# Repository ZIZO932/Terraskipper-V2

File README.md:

# Terraskipper V2 

> A mudskipper-inspired soft robot built to help farmers monitor and understand their soil

---

## What is this?

Terraskipper is a robot that moves like a mudskipper fish. It crawls on mud and uneven ground using fins powered by DC motors and servos. While it moves around it collects soil data like pH levels, moisture, salinity and other environmental readings.

The whole idea came from a real problem. The Nile Delta in Egypt is facing serious soil degradation. Salt levels are rising and pH is shifting in ways that hurt farming. Most monitoring tools cant really reach difficult terrain or muddy areas. Terraskipper can.

The robot is designed to go where normal sensors cant and give farmers useful data about their land without them having to do much.

---

## Why I made it

I wanted to build something that actually solves a problem in the real world not just a cool robot for the sake of it. Agriculture in Egypt especially near the Nile Delta depends on soil quality and right now that soil is changing in ways that are hard to track.

A mudskipper felt like the perfect inspiration because it literally evolved to handle the transition between water and land which is exactly the kind of terrain that is hard for robots to deal with.

---

## Build Process

After the design was done I moved on to actually building it. A lot of stuff that worked on screen didnt work the same in real life.

- Rebuilt the circuit from the schematic one component at a time, testing power, then the Pico, then each sensor one by one (moisture, TDS, temperature, the 3 ultrasonics) so debugging was easier.
- Got PCB review feedback: add screw mounting, clean up and round the layout, include Gerber files, add the missing sensors to the CAD. Fixed all of it and gave the PCB its own mounting spot in the 3D model.
- Assembled the robot: joined the two printed body halves, built the sensor placement mechanism, mounted the motors and fins, then fit the PCB and wired everything inside the body.
- Tested the full system and tested power, sensors, and movement again after assembly to catch anything that shifted.
- Uploaded and ran the code function by function. Found the right DC motor wasnt moving, swapped both motors to confirm it wasnt the motor itself, traced it to the motor driver's motor B output, and fixed it.
- Did a final pass before filming: checked all connections, cleaned up the wiring, and ran through the movements a few times to make sure they'd look good on camera.

---

## The Final Build

after the first prototype i went back and reprinted the whole body smaller than before. still fits everything inside the same as before, just uses less filament and ends up alot lighter overall. checked all the parts lined up right after printing and made a couple small tweaks where they didnt.

that was really the only change from the first prototype to the final one, just the size.

---

## How it works

The robot has two main systems working together

**Movement system**
- Two JGB37-520 DC Geared Motors (12V 37RPM with encoders) power the pectoral fins for forward movement
- One servo controls the caudal fin for steering
- Two more servos handle the sensor placement mechanism so the sensors can move up and down to properly contact the soil

**Sensor system**
- 3x HC-SR04 ultrasonic sensors for obstacle detection and movement awareness (removed two in the final because one of them wasnt working for no reason)
- MPU-6050 IMU for tilt and orientation tracking using gyroscope and accelerometer
- Ublox NEO-7M GPS module for location tracking
- Capacitive soil moisture sensor V2.0 for soil water content readings
- DS18B20 waterproof temperature sensor for soil temperature

**Brain**
- Raspberry Pi Pico 2 W handles everything

---

## The 3D Model

For the body i made sure that all edges have fillets and chamfers so the robot doesnt damage the soil while crawling.

The sensor placement mechanism uses a mini linear slider with a servo motor so the sensors can move vertically and make proper contact with different soil surfaces. The mechanism is also detachable so it can be removed for repairs without taking apart the whole robot.

---

## PCB & Electronics

The PCB is a 2-layer board. Top layer carries signal lines and positive voltage. Bottom layer is a full GND plane to keep things clean and reduce noise.

Main components on the board:

- Xiao esp S3
- 2x BTS7960 43A motor drivers (one per DC motor)
- XL4016 8A and LM2596 3A buck converters for power regulation
- MPU-6050 IMU gyro and accelerometer
- Ublox NEO-7M GPS module
- Capacitive soil moisture sensor V2.0
- DS18B20 waterproof temperature sensor
- 3x HC-SR04 ultrasonic sensors

All sensors run on 3.3V logic to match the Pico 2 W. Power comes from the buck converters and sensors pull directly from the Pico 3.3V output.

---

## Wiring

All connections go through the custom PCB. Motor drivers connect directly to the DC motors and are controlled via PWM from the Pico.

---

## Bill of Materials

18 components total. Estimated cost around **$102.50 USD / 5,315 EGP**

| Component | Category | Qty | Unit Price (EGP) | Total (EGP) |
|---|---|---|---|---|
| Raspberry pi Pico 2w | Microcontroller | 1 | 900 | 900 |
| BTS7960 43A DC Motor Driver | Motor Driver | 2 | 450 | 900 |
| MG996R 360° Servo Motor | Motors | 3 | 210 | 630 |
| DC Motor With Gear Box JGA25-370 12V 33RPM 30Kg.cm | Motors | 2 | 300 | 600 |
| Ublox NEO-7M GPS Module | Sensors | 1 | 540 | 540 |
| MPU-6050 IMU Gyro/Accel Module | Sensors | 1 | 175 | 175 |
| Capacitive Soil Moisture Sensor V2.0 | Sensors | 1 | 100 | 100 |
| DS18B20 Waterproof Temp Sensor | Sensors | 1 | 85 | 85 |
| HC-SR04 Ultrasonic Sensor | Sensors | 3 | 40 | 120 |
| Rechargeable Li-ion Battery Pack 18650 12V 6000mAh | Power | 1 | 900 | 900 |
| XL4016 8A Step-Down Buck Converter | Power | 1 | 243 | 243 |
| LM2596 3A Step-Down Buck Converter | Power | 1 | 122 | 122 |
| **Total** | | **18** | | **5,315 EGP** |

---

## Magazine / Zine

## Demo video

https://youtube.com/shorts/rW8oGuy9Nso

---

## Build Progress

The robot went through a lot of iterations. Some highlights:

- Switched from ESP32 to Raspberry Pi Pico 2 W midway through because it uses Python which is way better for me and had easier integration
- Replaced front servo motors with DC geared motors for more torque
- Rebuilt the schematic from scratch after finding SMD components weren't practical
- Redesigned the body twice to reduce filament usage and fit standard printer sizes
- Learned PID control to improve movement stability
- Took the PCB through a full review round, fixing mounting, layout, and Gerber file gaps
- Got the full system running together for the first time and debugged a motor driver fault on the way
- Reprinted the body smaller for the final version to cut weight and material

---

## Made by

Ziad — as part of a project exploring how robotics and soft robot design can support smart farming and environmental monitoring in Egypt

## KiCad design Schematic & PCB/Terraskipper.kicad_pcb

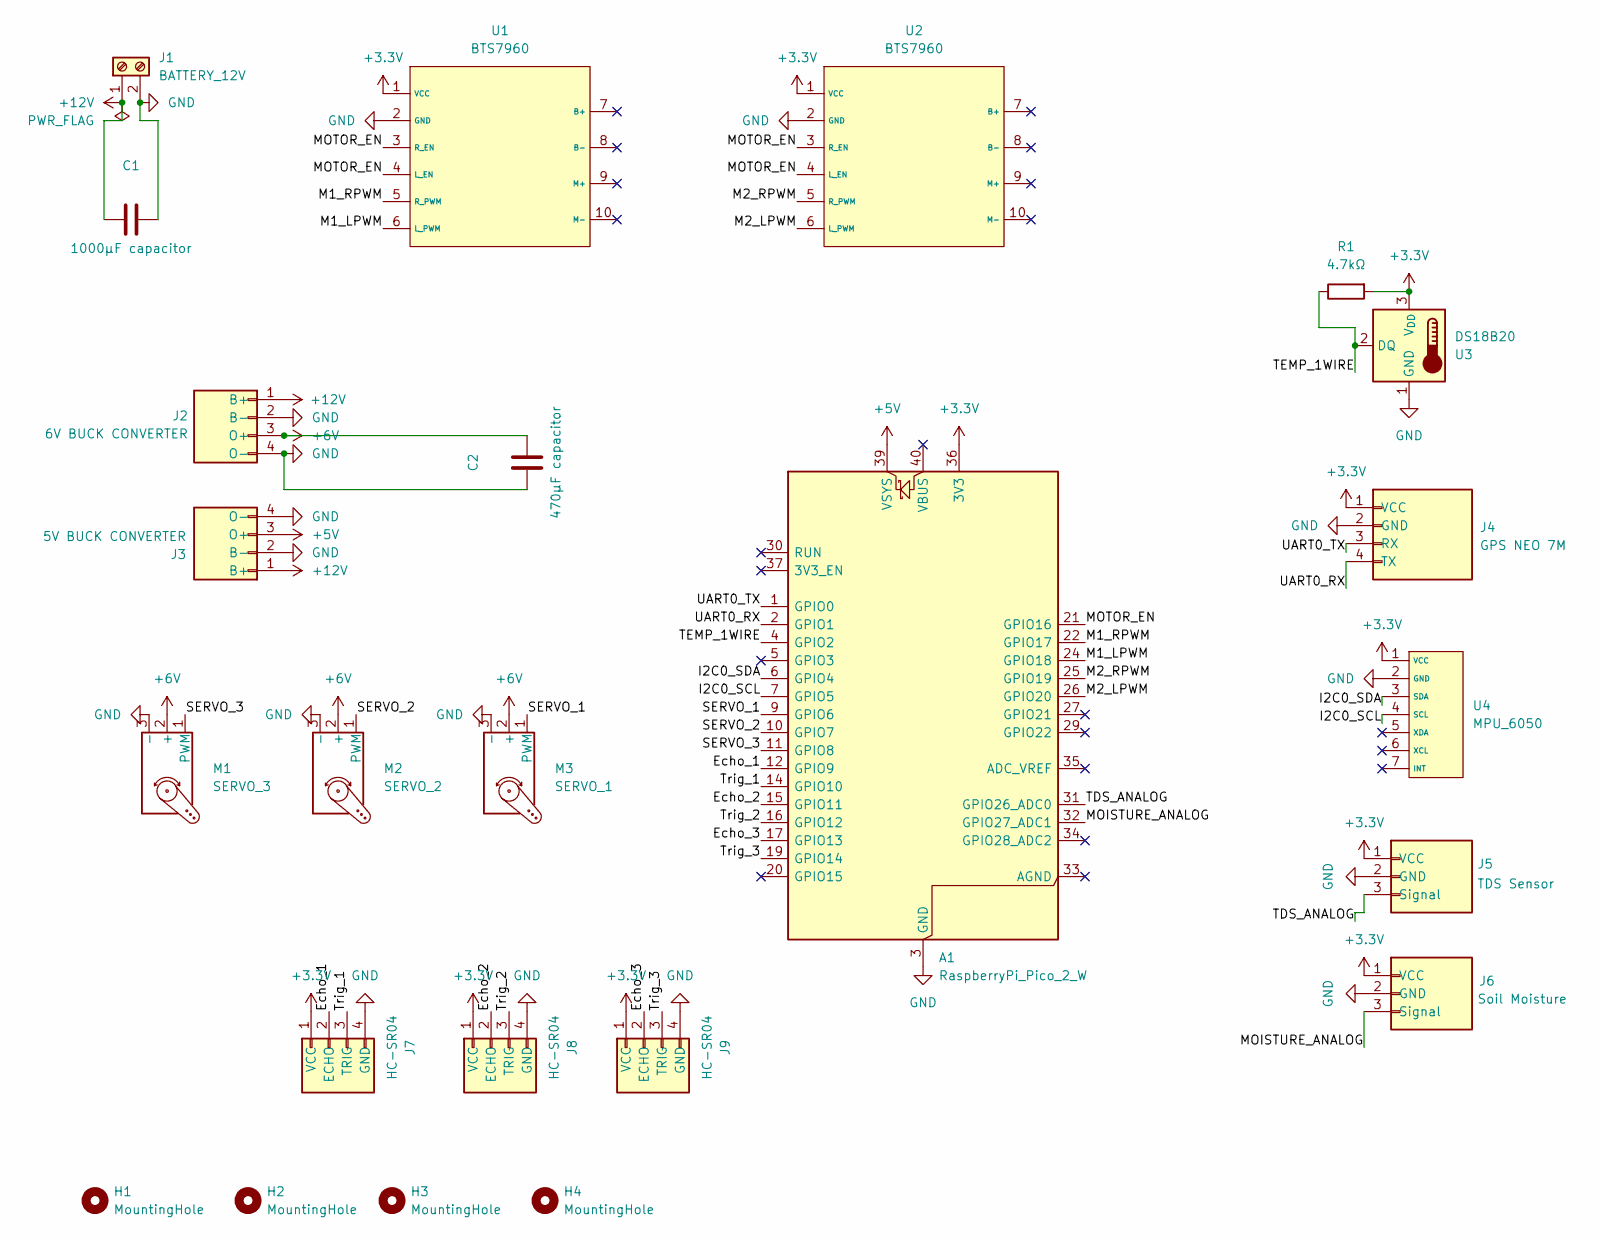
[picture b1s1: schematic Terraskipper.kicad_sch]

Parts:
A1: RaspberryPi_Pico_2_W; RaspberryPi_Pico_Common_Unspecified
C1: 1000µF capacitor; CP_Axial_L10.0mm_D4.5mm_P15.00mm_Horizontal
C2: 470µF capacitor; CP_Axial_L10.0mm_D4.5mm_P15.00mm_Horizontal
H1, H2, H3, H4: MountingHole; MountingHole_2.1mm
J1: BATTERY_12V; PhoenixContact_MSTBVA_2,5_2-G-5,08_1x02_P5.08mm_Vertical
J2: 6V BUCK CONVERTER; PinHeader_1x04_P2.54mm_Vertical
J3: 5V BUCK CONVERTER; PinHeader_1x04_P2.54mm_Vertical
J4: GPS NEO 7M; PinHeader_1x04_P2.54mm_Vertical
J5: TDS Sensor; PinHeader_1x03_P2.54mm_Vertical
J6: Soil Moisture; PinHeader_1x03_P2.54mm_Vertical
J7, J8, J9: HC-SR04; PinHeader_1x04_P2.54mm_Vertical
M1: SERVO_3; PinHeader_1x03_P2.54mm_Vertical
M2: SERVO_2; PinHeader_1x03_P2.54mm_Vertical
M3: SERVO_1; PinHeader_1x03_P2.54mm_Vertical
R1: 4.7kΩ; R_Axial_DIN0204_L3.6mm_D1.6mm_P7.62mm_Horizontal
U1, U2: BTS7960; PinHeader_1x06_P2.54mm_Vertical
U3: DS18B20; TO-92_Inline
U4: MPU_6050; PinHeader_1x07_P2.54mm_Vertical_SMD_Pin1Left

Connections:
+3.3V: A1.36 (3V3), J4.1 (VCC), J5.1 (VCC), J6.1 (VCC), J7.1 (VCC), J8.1 (VCC), J9.1 (VCC), R1.2, U1.1 (VCC), U2.1 (VCC), U3.3 (V_{DD}), U4.1 (VCC)
+5V: A1.39 (VSYS), J3.3 (O+)
+6V: C2.1, J2.3 (O+), M1.2 (+), M2.2 (+), M3.2 (+)
+12V: C1.1, J1.1, J2.1 (B+), J3.1 (B+)
/Echo_1: A1.12 (GPIO9), J7.2 (ECHO)
/Echo_2: A1.15 (GPIO11), J8.2 (ECHO)
/Echo_3: A1.17 (GPIO13), J9.2 (ECHO)
/I2C0_SCL: A1.7 (GPIO5), U4.4 (SCL)
/I2C0_SDA: A1.6 (GPIO4), U4.3 (SDA)
/M1_LPWM: A1.24 (GPIO18), U1.6 (L_PWM)
/M1_RPWM: A1.22 (GPIO17), U1.5 (R_PWM)
/M2_LPWM: A1.26 (GPIO20), U2.6 (L_PWM)
/M2_RPWM: A1.25 (GPIO19), U2.5 (R_PWM)
/MOISTURE_ANALOG: A1.32 (GPIO27_ADC1), J6.3 (Signal)
/MOTOR_EN: A1.21 (GPIO16), U1.3 (R_EN), U1.4 (L_EN), U2.3 (R_EN), U2.4 (L_EN)
/SERVO_1: A1.9 (GPIO6), M3.1 (PWM)
/SERVO_2: A1.10 (GPIO7), M2.1 (PWM)
/SERVO_3: A1.11 (GPIO8), M1.1 (PWM)
/TDS_ANALOG: A1.31 (GPIO26_ADC0), J5.3 (Signal)
/TEMP_1WIRE: A1.4 (GPIO2), R1.1, U3.2 (DQ)
/Trig_1: A1.14 (GPIO10), J7.3 (TRIG)
/Trig_2: A1.16 (GPIO12), J8.3 (TRIG)
/Trig_3: A1.19 (GPIO14), J9.3 (TRIG)
/UART0_RX: A1.2 (GPIO1), J4.4 (TX)
/UART0_TX: A1.1 (GPIO0), J4.3 (RX)
GND: A1.3 (GND), A1.8 (GND), A1.13 (GND), A1.18 (GND), A1.23 (GND), A1.28 (GND), A1.38 (GND), C1.2, C2.2, J1.2, J2.2 (B-), J2.4 (O-), J3.2 (B-), J3.4 (O-), J4.2 (GND), J5.2 (GND), J6.2 (GND), J7.4 (GND), J8.4 (GND), J9.4 (GND), M1.3 (-), M2.3 (-), M3.3 (-), U1.2 (GND), U2.2 (GND), U3.1 (GND), U4.2 (GND)

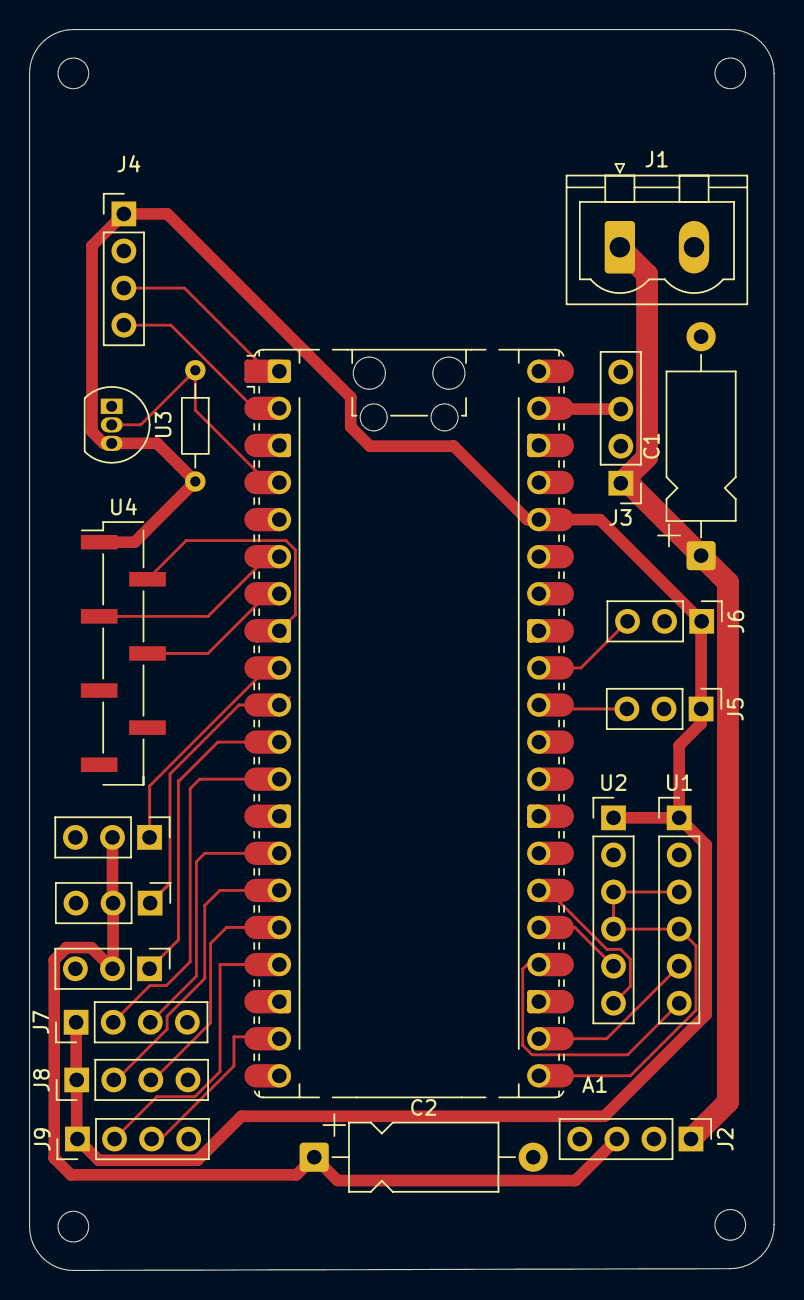
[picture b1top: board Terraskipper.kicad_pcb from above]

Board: 2 copper layers, 51.0 x 85.0 mm, 24 parts (0 on the bottom side), 26 nets.
